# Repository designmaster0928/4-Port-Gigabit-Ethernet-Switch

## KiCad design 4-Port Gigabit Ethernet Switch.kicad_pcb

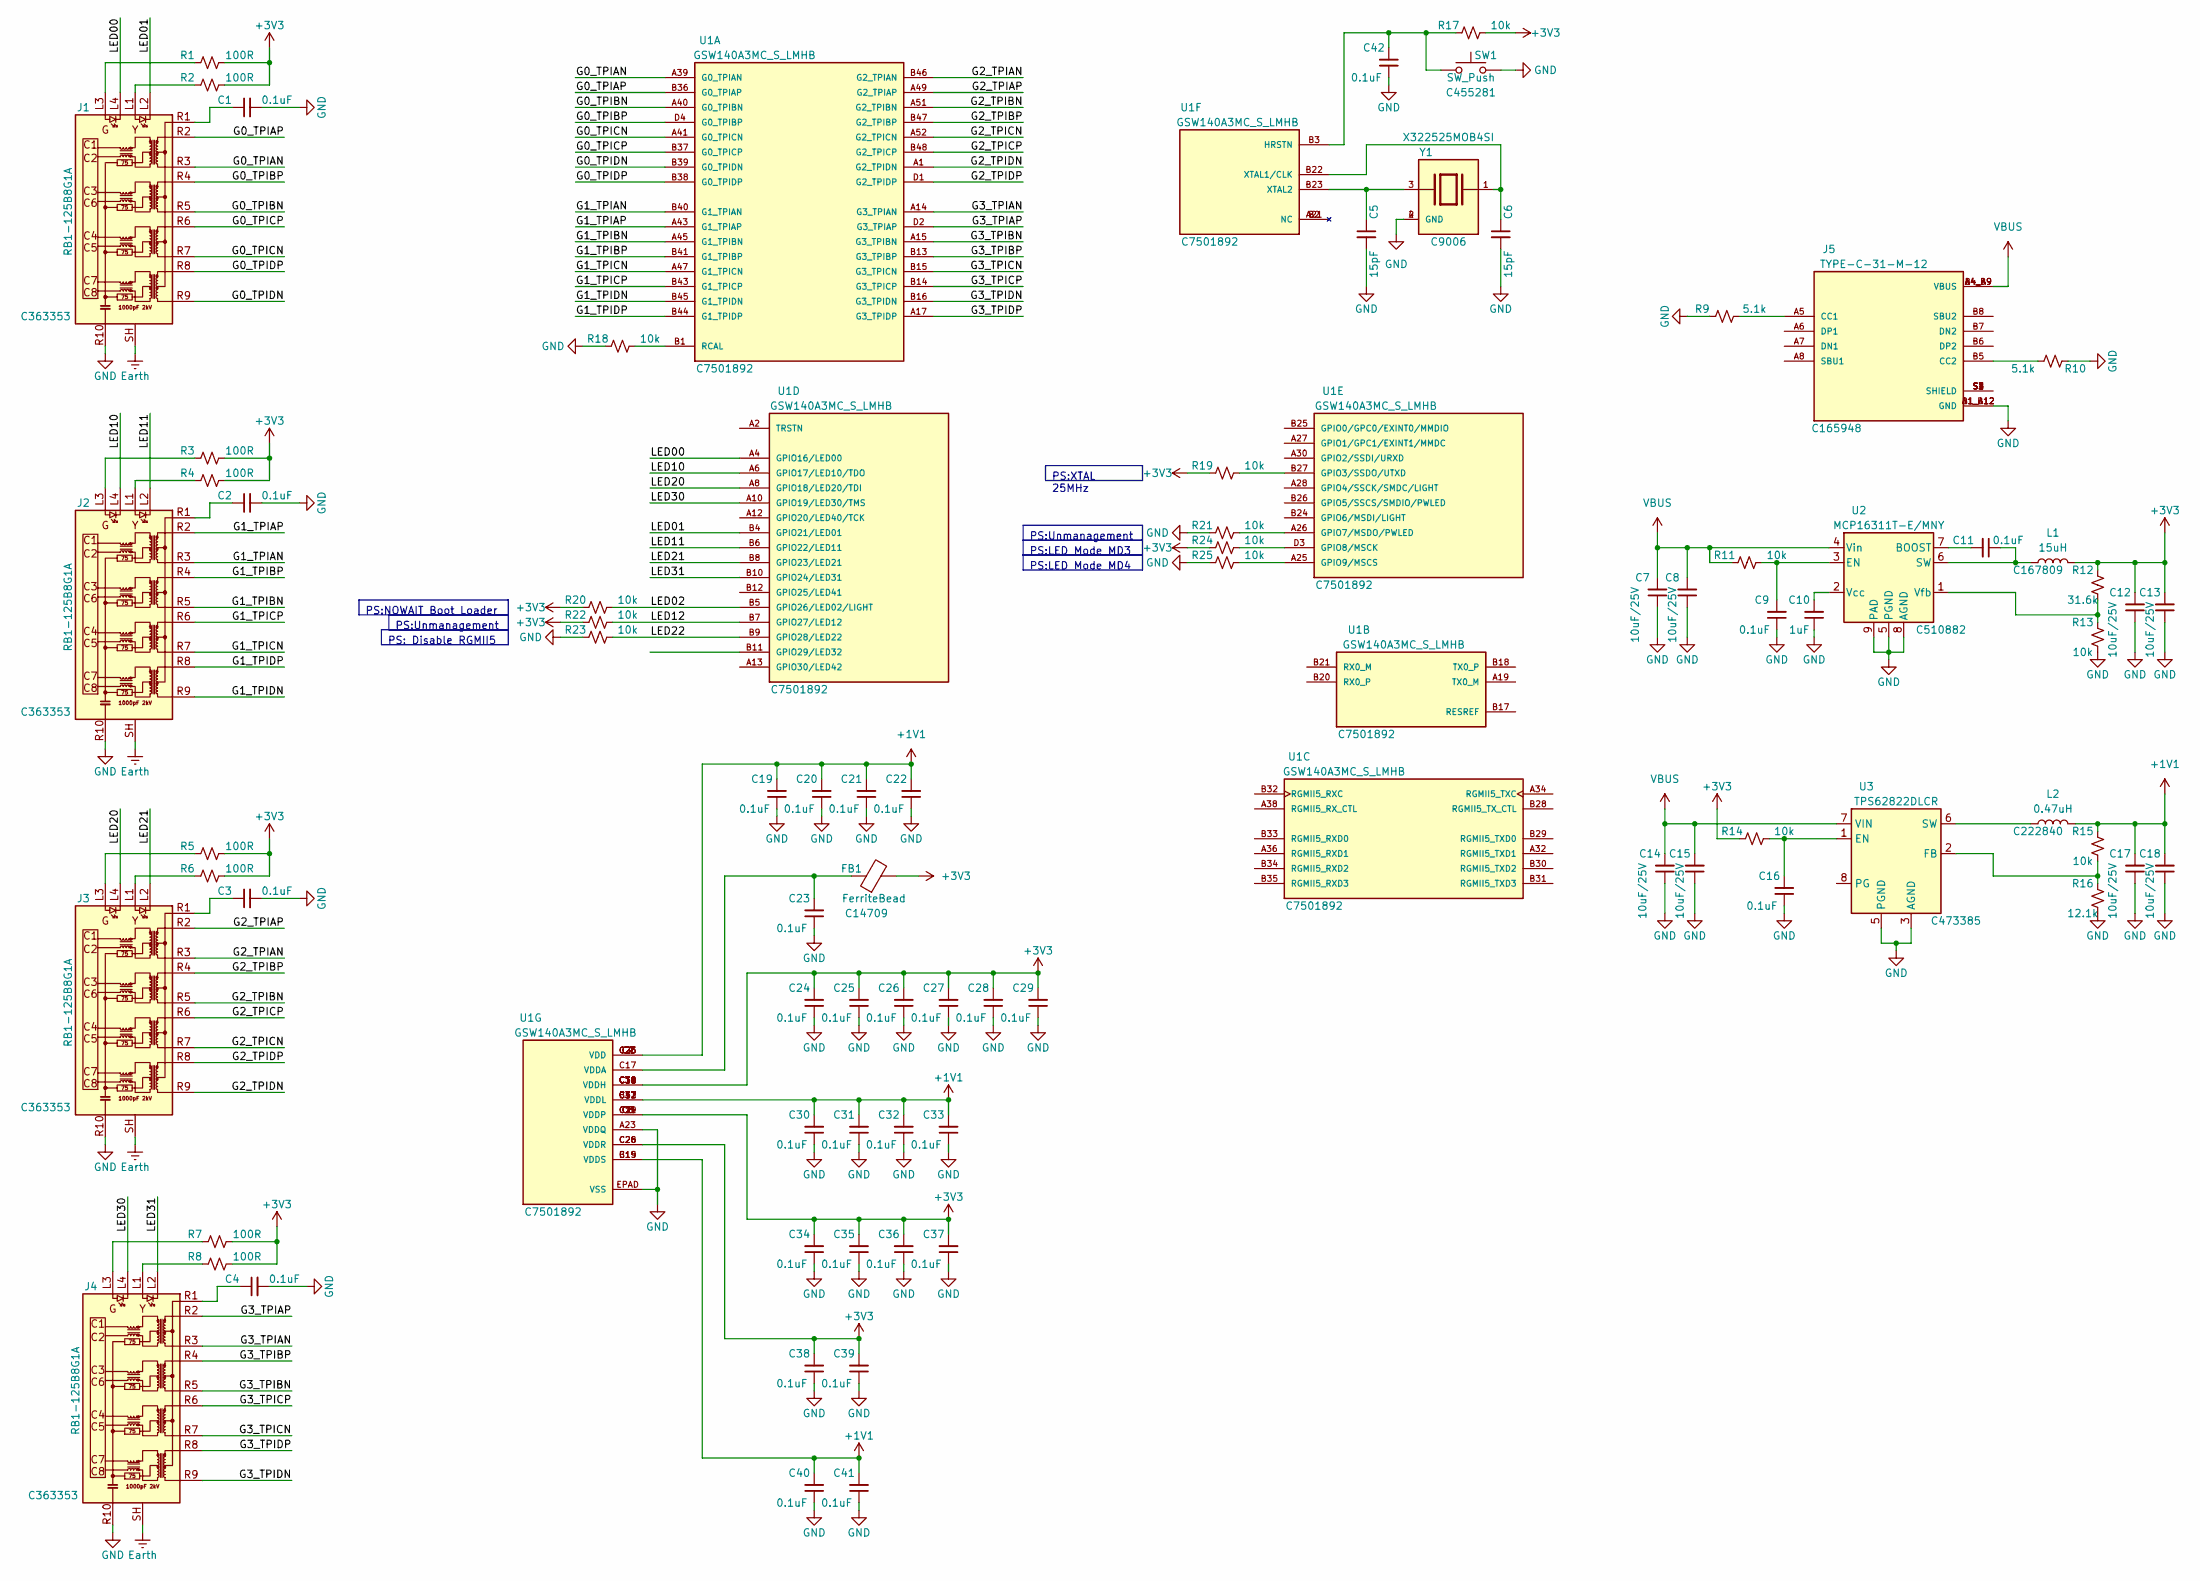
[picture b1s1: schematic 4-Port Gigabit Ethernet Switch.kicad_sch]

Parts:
C1, C2, C3, C4, C9, C11, C16, C19, C20, C21, C22, C23, C24, C25, C26, C27, C28, C29, C30, C31, C32, C33, C34, C35, C36, C37, C38, C39, C40, C41, C42: 0.1uF; C_0402_1005Metric; LCSC C105883
C5, C6: 15pF; C_0402_1005Metric; LCSC C106997
C7, C8, C12, C13, C14, C15, C17, C18: 10uF/25V; C_0805_2012Metric; LCSC C89831
C10: 1uF; C_0603_1608Metric; LCSC C14664
FB1: FerriteBead; L_0603_1608Metric; LCSC C14709
J1, J2, J3, J4: RB1-125B8G1A; RJ45_UDE_RB1-125B8G1A; LCSC C363353
J5: TYPE-C-31-M-12; HRO_TYPE-C-31-M-12; PARTREV 2020.12.08; LCSC C165948
L1: 15uH; L_Bourns-SRN4018; LCSC C167809
L2: 0.47uH; L_Taiyo-Yuden_NR-24xx; LCSC C222840
R1, R2, R3, R4, R5, R6, R7, R8: 100R; R_0402_1005Metric; LCSC C106232
R9, R10: 5.1k; R_0402_1005Metric; LCSC C105872
R11, R13, R14, R15, R17, R18, R19, R20, R21, R22, R23, R24, R25: 10k; R_0402_1005Metric; LCSC C60490
R12: 31.6k; R_0402_1005Metric; LCSC C276265
R16: 12.1k; R_0402_1005Metric; LCSC C132157
SW1: SW_Push; SW_Push_SPST_NO_Alps_SKRK; LCSC C455281
U1: GSW140A3MC_S_LMHB; XCVR_GSW140A3MC_S_LMHB; PARTREV 1.11mm; LCSC C7501892
U2: MCP16311T-E/MNY; DFN-8-1EP_3x2mm_P0.5mm_EP1.75x1.45mm; LCSC C510882
U3: TPS62822DLCR; Texas_VSON-HR-8_1.5x2mm_P0.5mm; LCSC C473385
Y1: X322525MOB4SI; XTAL_ABM8G-25.000MHZ-B4Y-T; LCSC C9006

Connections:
+1V1: C17.2, C18.2, C19.2, C20.2, C21.2, C22.2, C30.2, C31.2, C32.2, C33.2, C40.2, C41.2, L2.2, R15.2, U1.B19 (VDDS), U1.B42 (VDDL), U1.C2 (VDD), U1.C4 (VDD), U1.C12 (VDDL), U1.C15 (VDDS), U1.C23 (VDD), U1.C25 (VDD), U1.C33 (VDDL), U1.C37 (VDDL)
+3V3: C12.2, C13.2, C24.2, C25.2, C26.2, C27.2, C28.2, C29.2, C34.2, C35.2, C36.2, C37.2, C38.2, C39.2, FB1.2, L1.2, R1.2, R2.2, R3.2, R4.2, R5.2, R6.2, R7.2, R8.2, R12.2, R14.1, R17.2, R19.1, R20.1, R22.1, R24.1, U1.C6 (VDDP), U1.C8 (VDDP), U1.C10 (VDDH), U1.C14 (VDDH), U1.C19 (VDDP), U1.C21 (VDDP), U1.C26 (VDDR), U1.C28 (VDDR), U1.C31 (VDDH), U1.C34 (VDDH), U1.C36 (VDDH), U1.C39 (VDDH)
/G0_TPIAN: J1.R3 (TD1-), U1.A39 (G0_TPIAN)
/G0_TPIAP: J1.R2 (TD1+), U1.B36 (G0_TPIAP)
/G0_TPIBN: J1.R5 (TD2-), U1.A40 (G0_TPIBN)
/G0_TPIBP: J1.R4 (TD2+), U1.D4 (G0_TPIBP)
/G0_TPICN: J1.R7 (TD3-), U1.A41 (G0_TPICN)
/G0_TPICP: J1.R6 (TD3+), U1.B37 (G0_TPICP)
/G0_TPIDN: J1.R9 (TD4-), U1.B39 (G0_TPIDN)
/G0_TPIDP: J1.R8 (TD4+), U1.B38 (G0_TPIDP)
/G1_TPIAN: J2.R3 (TD1-), U1.B40 (G1_TPIAN)
/G1_TPIAP: J2.R2 (TD1+), U1.A43 (G1_TPIAP)
/G1_TPIBN: J2.R5 (TD2-), U1.A45 (G1_TPIBN)
/G1_TPIBP: J2.R4 (TD2+), U1.B41 (G1_TPIBP)
/G1_TPICN: J2.R7 (TD3-), U1.A47 (G1_TPICN)
/G1_TPICP: J2.R6 (TD3+), U1.B43 (G1_TPICP)
/G1_TPIDN: J2.R9 (TD4-), U1.B45 (G1_TPIDN)
/G1_TPIDP: J2.R8 (TD4+), U1.B44 (G1_TPIDP)
/G2_TPIAN: J3.R3 (TD1-), U1.B46 (G2_TPIAN)
/G2_TPIAP: J3.R2 (TD1+), U1.A49 (G2_TPIAP)
/G2_TPIBN: J3.R5 (TD2-), U1.A51 (G2_TPIBN)
/G2_TPIBP: J3.R4 (TD2+), U1.B47 (G2_TPIBP)
/G2_TPICN: J3.R7 (TD3-), U1.A52 (G2_TPICN)
/G2_TPICP: J3.R6 (TD3+), U1.B48 (G2_TPICP)
/G2_TPIDN: J3.R9 (TD4-), U1.A1 (G2_TPIDN)
/G2_TPIDP: J3.R8 (TD4+), U1.D1 (G2_TPIDP)
/G3_TPIAN: J4.R3 (TD1-), U1.A14 (G3_TPIAN)
/G3_TPIAP: J4.R2 (TD1+), U1.D2 (G3_TPIAP)
/G3_TPIBN: J4.R5 (TD2-), U1.A15 (G3_TPIBN)
/G3_TPIBP: J4.R4 (TD2+), U1.B13 (G3_TPIBP)
/G3_TPICN: J4.R7 (TD3-), U1.B15 (G3_TPICN)
/G3_TPICP: J4.R6 (TD3+), U1.B14 (G3_TPICP)
/G3_TPIDN: J4.R9 (TD4-), U1.B16 (G3_TPIDN)
/G3_TPIDP: J4.R8 (TD4+), U1.A17 (G3_TPIDP)
/LED00: J1.L4, U1.A4 (GPIO16/LED00)
/LED01: J1.L2, U1.B4 (GPIO21/LED01)
/LED02: R20.2, U1.B5 (GPIO26/LED02/LIGHT)
/LED10: J2.L4, U1.A6 (GPIO17/LED10/TDO)
/LED11: J2.L2, U1.B6 (GPIO22/LED11)
/LED12: R22.2, U1.B7 (GPIO27/LED12)
/LED20: J3.L4, U1.A8 (GPIO18/LED20/TDI)
/LED21: J3.L2, U1.B8 (GPIO23/LED21)
/LED22: R23.2, U1.B9 (GPIO28/LED22)
/LED30: J4.L4, U1.A10 (GPIO19/LED30/TMS)
/LED31: J4.L2, U1.B10 (GPIO24/LED31)
Earth: J1.SH, J2.SH, J3.SH, J4.SH
GND: C1.2, C2.2, C3.2, C4.2, C5.2, C6.2, C7.1, C8.1, C9.1, C10.1, C12.1, C13.1, C14.1, C15.1, C16.1, C17.1, C18.1, C19.1, C20.1, C21.1, C22.1, C23.1, C24.1, C25.1, C26.1, C27.1, C28.1, C29.1, C30.1, C31.1, C32.1, C33.1, C34.1, C35.1, C36.1, C37.1, C38.1, C39.1, C40.1, C41.1, C42.1, J1.R10 (GND), J2.R10 (GND), J3.R10 (GND), J4.R10 (GND), J5.A1_B12 (GND), J5.B1_A12 (GND), R9.1, R10.1, R13.1, R16.1, R18.1, R21.1, R23.1, R25.1, SW1.2, U1.A23 (VDDQ), U1.EPAD (VSS), U2.5 (PGND), U2.8 (AGND), U2.9 (PAD), U3.3 (AGND), U3.5 (PGND), Y1.2 (GND), Y1.4 (GND)
unnamed: C1.1, J1.R1 (CT)
unnamed: J1.L1, R2.1
unnamed: J1.L3, R1.1
unnamed: C2.1, J2.R1 (CT)
unnamed: J2.L1, R4.1
unnamed: J2.L3, R3.1
unnamed: C3.1, J3.R1 (CT)
unnamed: J3.L1, R6.1
unnamed: J3.L3, R5.1
unnamed: C4.1, J4.R1 (CT)
unnamed: J4.L1, R8.1
unnamed: J4.L3, R7.1
unnamed: J5.A5 (CC1), R9.2
unnamed: J5.B5 (CC2), R10.2
unnamed: J5.S1 (SHIELD), J5.S2 (SHIELD), J5.S3 (SHIELD), J5.S4 (SHIELD)
unnamed: R18.2, U1.B1 (RCAL)
unnamed: R19.2, U1.B27 (GPIO3/SSDO/UTXD)
unnamed: R21.2, U1.A26 (GPIO7/MSDO/PWLED)
unnamed: R24.2, U1.D3 (GPIO8/MSCK)
unnamed: R25.2, U1.A25 (GPIO9/MSCS)
unnamed: C42.2, R17.1, SW1.1, U1.B3 (HRSTN)
unnamed: C6.1, U1.B22 (XTAL1/CLK), Y1.1
unnamed: C5.1, U1.B23 (XTAL2), Y1.3
unnamed: C23.2, FB1.1, U1.C17 (VDDA)
unnamed: C11.2, U2.7 (BOOST)
unnamed: C9.2, R11.2, U2.3 (EN)
unnamed: C11.1, L1.1, U2.6 (SW)
unnamed: C10.2, U2.2 (Vcc)
unnamed: R12.1, R13.2, U2.1 (Vfb)
unnamed: C16.2, R14.2, U3.1 (EN)
unnamed: R15.1, R16.2, U3.2 (FB)
unnamed: L2.1, U3.6 (SW)
VBUS: C7.2, C8.2, C14.2, C15.2, J5.A4_B9 (VBUS), J5.B4_A9 (VBUS), R11.1, U2.4 (Vin), U3.7 (VIN)

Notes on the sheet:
PS:Unmanagement
PS:NOWAIT Boot Loader
PS: Disable RGMII5
PS:LED Mode MD3
PS:XTAL 25MHz
PS:LED Mode MD4

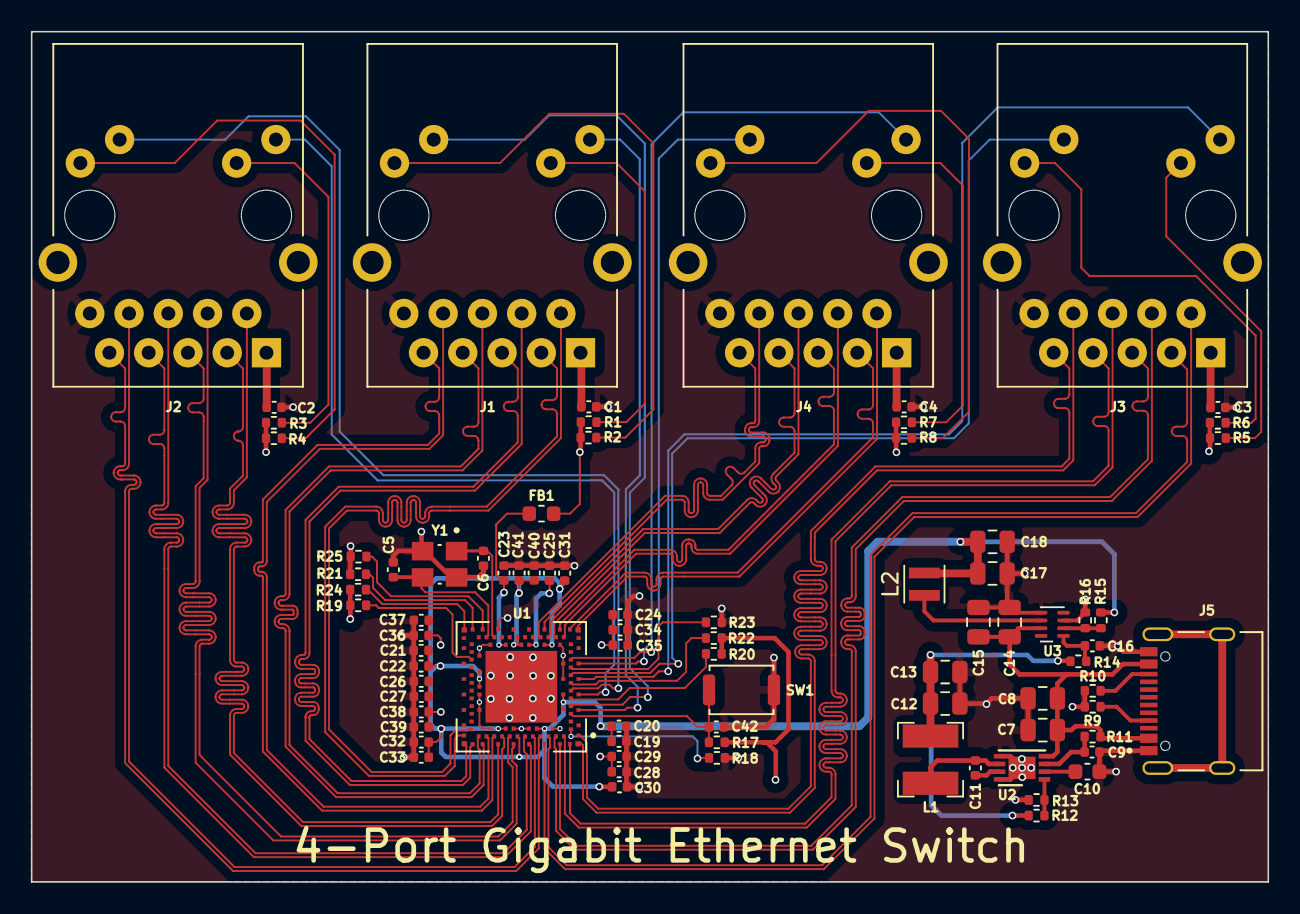
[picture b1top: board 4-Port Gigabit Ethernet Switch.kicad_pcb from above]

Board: 4 copper layers, 80.0 x 55.0 mm, 80 parts (0 on the bottom side), 80 nets.

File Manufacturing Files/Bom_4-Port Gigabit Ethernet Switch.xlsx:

Comment | Designator | Footprint | LCSC Part Number | Qty
0.1uF | C1, C2, C3, C4, C9, C11, C16, C19, C20, C21, C22, C23, C24, C25, C26, C27, C28,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 | Capacitor_SMD:C_0402_1005Metric | C105883 | 31
15pF | C5, C6 | Capacitor_SMD:C_0402_1005Metric | C106997 | 2
10uF/25V | C7, C8, C12, C13, C14, C15, C17, C18 | Capacitor_SMD:C_0805_2012Metric | C89831 | 8
1uF | C10 | Capacitor_SMD:C_0603_1608Metric | C14664 | 1
FerriteBead | FB1 | Inductor_SMD:L_0603_1608Metric | C14709 | 1
RB1-125B8G1A | J1, J2, J3, J4 | Connector_RJ:RJ45_UDE_RB1-125B8G1A | C363353 | 4
TYPE-C-31-M-12 | J5 | TYPE-C-31-M-12:HRO_TYPE-C-31-M-12 | C165948 | 1
15uH | L1 | Inductor_SMD:L_Bourns-SRN4018 | C167809 | 1
0.47uH | L2 | Inductor_SMD:L_Taiyo-Yuden_MD-2020 | C222840 | 1
100R | R1, R2, R3, R4, R5, R6, R7, R8 | Resistor_SMD:R_0402_1005Metric | C106232 | 8
5.1k | R9, R10 | Resistor_SMD:R_0402_1005Metric | C105872 | 2
10k | R11, R13, R14, R15, R17, R18, R19, R20, R21, R22, R23, R24, R25 | Resistor_SMD:R_0402_1005Metric | C60490 | 13
31.6k | R12 | Resistor_SMD:R_0402_1005Metric | C276265 | 1
12.1k | R16 | Resistor_SMD:R_0402_1005Metric | C132157 | 1
SW_Push | SW1 | Button_Switch_SMD:SW_Push_SPST_NO_Alps_SKRK | C455281 | 1
GSW140A3MC_S_LMHB | U1 | GSW140A3MC_S_LMHB:XCVR_GSW140A3MC_S_LMHB | C7501892 | 1
MCP16311T-E/MNY | U2 | Package_DFN_QFN:DFN-8-1EP_3x2mm_P0.5mm_EP1.75x1.45mm | C510882 | 1
TPS62822DLCR | U3 | Package_DFN_QFN:Texas_VSON-HR-8_1.5x2mm_P0.5mm | C473385 | 1
ABM8G-25.000MHZ-B4Y-T | Y1 | ABM8G-25.000MHZ-B4Y-T:XTAL_ABM8G-25.000MHZ-B4Y-T | C9006 | 1

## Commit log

2023-10-01 Added-23/10/01
